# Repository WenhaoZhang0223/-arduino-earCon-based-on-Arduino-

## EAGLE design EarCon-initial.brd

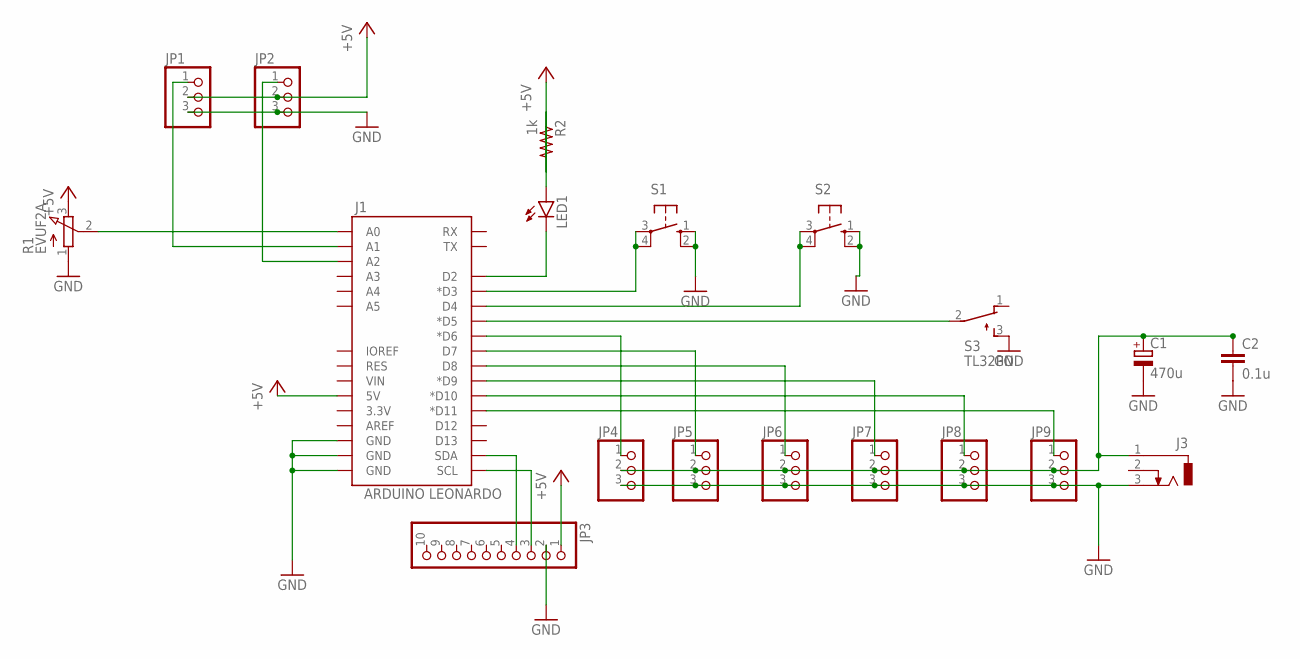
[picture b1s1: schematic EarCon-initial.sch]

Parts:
C1: 470u; E5-10,5
C2: 0.1u; C050-025X075
J1: ARDUINO LEONARDO; UNO_R3_SHIELD_NOLABELS
J3: DCJ0303
JP1, JP2, JP4, JP5, JP6, JP7, JP8, JP9: PINHD-1X3; 1X03
JP3: PINHD-1X10; 1X10
LED1: LED5MM
R1: EVUF2A; EVUF
R2: 1k; 0204/7
S1, S2: 10-XX; B3F-10XX
S3: TL32PO; TL3XPO

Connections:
+5V: J1.5V, JP1.2, JP2.2, JP3.1, R1.3 (E), R2.2
GND: C1.-, C2.2, J1.GND@0 (GND), J1.GND@1 (GND), J1.GND@2 (GND), J3.3, JP1.3, JP2.3, JP3.2, JP4.3, JP5.3, JP6.3, JP7.3, JP8.3, JP9.3, R1.1 (A), S1.1 (S), S1.2 (S1), S2.1 (S), S2.2 (S1), S3.3 (S)
unnamed: J1.A0, R1.2 (S)
unnamed: J1.A1, JP1.1
unnamed: J1.A2, JP2.1
unnamed: J1.SDA, JP3.4
unnamed: J1.SCL, JP3.3
unnamed: J1.D11 (*D11), JP9.1
unnamed: J1.D10 (*D10), JP8.1
unnamed: J1.D9 (*D9), JP7.1
unnamed: J1.D8, JP6.1
unnamed: J1.D7, JP5.1
unnamed: J1.D6 (*D6), JP4.1
unnamed: C1.+, C2.1, J3.1, JP4.2, JP5.2, JP6.2, JP7.2, JP8.2, JP9.2
unnamed: LED1.A, R2.1
unnamed: J1.D2, LED1.K (C)
unnamed: J1.D3 (*D3), S1.3, S1.4 (P1)
unnamed: J1.D4, S2.3, S2.4 (P1)
unnamed: J1.D5 (*D5), S3.2

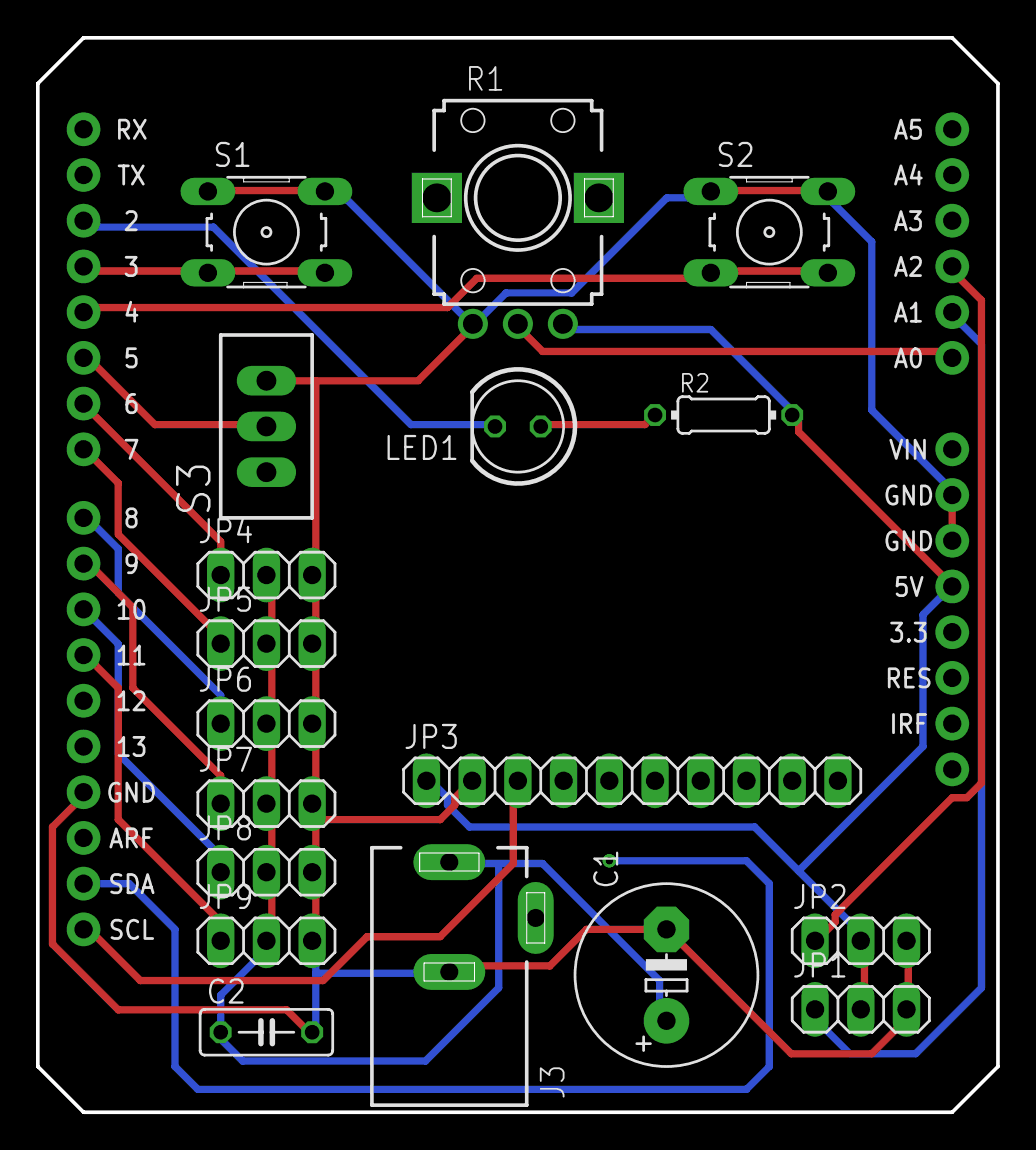
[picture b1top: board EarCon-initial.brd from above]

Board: 2 copper layers, 53.3 x 59.7 mm, 19 parts (0 on the bottom side), 19 nets.

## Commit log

2024-06-18 EarCon

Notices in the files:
parts and their libraries:
SparkFun-Boards: Licensing: CC v3.0 Share-Alike You are welcome to use this library for commercial purposes.
